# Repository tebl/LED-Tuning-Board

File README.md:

# LED Tuning Board

If you were to take a look at many of my repositories, you'll find that for someone who doesn't actually love having a bunch of LEDs on things, I seem to tell people to use a *whole* lot of them. There are projects where I've gone through several revisions, installing different colours on them so that I'd instantly be able to tell them apart. What you won't find is a lot of datasheets, because where I shop - you generally get a bag full of them, and nothing that you would call a datasheet. Perhaps I should shop in better places, but I just can't stop myself. And as for the end result, there are times where I'm straight up guessing at which value resistor to put in series with it. Sometimes it fails to light up, sometimes it'll blind people in the next room, and from time to time I get them *just right* because I had found the same bag of LEDs.

And after doing that for almost a decade, I knew it was time! It was time to change, it was time to get a variable bench power supply and a proper breadboard. Realizing that such PSUs cost far more than I would be willing to pay, and that I would never find a breadboard that I would consider *"good"*, I did what I always do: I designed something. I call it the *LED Tuning Board*.

Does it tune your LEDs? No. What it does is give you a way to quickly plug in various types of through-hole LEDs, and then allows you to quickly go through various combinations of resistors until you find something that *YOU* will find comfortable. Because *comfortable* is what you'll be willing to have sitting on your desk, no matter if that desk is in a brightly lit studio or the dank type of basements that I regularly seem to enjoy dwelling within.

At some point I wanted to do a whole video on the topic of the *LED Tuning Board*, but I miserably failed at coming up with sufficient amounts of puns in order to pull off 20 minutes worth of soldering an LED in different ways. Until I do, here's a short clip of me showing the thing in as short a time possible. RGB LEDs are a feature of it, but necessarily so - they're just three LEDs combined into the physical space of one. There are three *banks* of resistors, one for each - with a jumper next to it that hooks that end up to VCC or GND. Add more than one jumper to a single bank in order to put resistors in parallel, add a few DuPont wires between pins and you can easily put a banks resistor value in series with that of another bank.

Truly exciting stuff! And on that note, I also put a commonly available fuse on the board - for when things become slightly too exciting. 

# 1> Building the board
Soldering together the few components should be easy going as long as you have access to a reasonable set of tools, personally I'm using a cheap soldering station with adjustable temperature so there's no need really no need to offer up your hard-earned cash to the old Norse god, Hakko. Hakko is actually a well-known brand, not a Norse god as previously stated. I meant that as a joke, so please don't send me brand new Hakko gear as punishment (I would just end up using it). Go expensive if you want to, not because that one guy on the Internet told you to. Personally I prefer using 60/40 soldering tin, mostly as the lead-free stuff makes the job a lot harder when you're just getting into the hobby of soldering things together.

:warning: The subsequent images from the actual build process  were based on revision A of the project, this preview is of the updated design. The purpose of the change was to make the illustrations easier to read and understand, beyond that there are no changes. Enjoy building a copy of it that's better than the one I have!

Do, however, make sure to start by studying the PCB by itself. Both sides, perform dry fits where needed so that you have an idea of where everything should go. The latter is because removing a components is always a lot harder than getting it right in the first place. In particular, take care when it comes to the orientation of polarized components - these include electrolytic capacitors and diodes (match the orientation exactly, study the gallery images for reference). 

As for a first step though, I've just gone ahead and added the resistors to each of the resistor *banks*. While you could adapt things slightly by changing out some of the values, these are the most common values that anyone would probably have available in their parts-bin. Each of them should match up with a step on the pin header block next to it.

As for the remainder of the installation, I went in the direction of building a different version of the one covered by the schematic. Mainly because I did not have the LM317 variable regulator available when building it, so I instead made changes to the circuit by building one with a 3.3v regulator instead. Check out the proceeding subheadings for details on the construction of either of them.

Before doing all that, I did add a 1N5819 Schottky diode - that's there to keep things from exploding if you were to plug in a power supply with the incorrect polarity. For that you also need to ensure that you actually install it the right way, meaning that the little silver stripe should match up with the white stripe on the board.

## 1.1> 3.3v fixed regulator
My choice of the *LD1117AV33*, a 3.3v regulator, was based on the thorough research of finding one in my parts-bin then throwing it in there. As they're not entirely the same, we'll need to make a few small adjustments when attempting to use it.

The first change is that C2 should have a greater value than the one printed, going up to 10uF instead of the sticking with the 1uF as marked. The resistors marked from R1 through R4 have also been skipped, we also no longer have a need for J3. We also need to install a small piece of wire on the back, some of the leftover clippings from one of resistors will be perfect.

:grey_question: The LD1117A-series of volage regulators have a wide range of output voltages available, I've simply picked 3.3v as with a 5v power input I end up with the two I need. If you want something else, there's also the *LD1117AV50* in case you explicitly wanted one that has 5v on the output.

## 1.2>  Variable voltage regulator
The *LM317* voltage regulator is the one I had in mind when building this version of the PCB, its main selling point is that we can easily generate several other voltages based on the choice of resistors installed on the board. With a common resistor (R1) as its base, we will get different selectable output voltages (V1/V2/V3) depending on the value of resistors R2, R3 and R4 - one for each of the generated outputs. One has been filled in for you along with a set base, that's R1 at 240 Ohm and R2 at 390 Ohm for a V1 = 3.28v.

That sounds like a lot of math that we need to do, but if you're going by the one suggested - we've already chosen a base resistor value (R1 = 240 Ohm). Basically we just need to pick whatever we want for R3/R4 by going up or down on the table, just know that we won't be able to generate a higher voltage than what we sufficiently provide it with. If you want to understand how exactly it works, either consult the datasheet included or you can go to the source of the table at [reuk.co.uk](http://www.reuk.co.uk/wordpress/electric-circuit/lm317-voltage-calculator/) for all of the relevant mathematical questions.

## 1.3> Moving on
With all of the neat details on the choice of voltage regulators taken care of, hopefully explained sufficiently that you know what was going on the whole time. As for the pictures we've been covering the installation of a fixed regulator, so when moving forwards we need to keep in mind that J3 will not be needed. You will, however, need it if you went with the variable option. 

Moving on with the installation, we've then done is to add all of the pin headers that are required. I've tried splashing a bit of colour here and there, mostly so that I remember that the red ones are the ones that requires that we know what we're doing (linking the block to either VCC on top, or GND on the bottom). The yellow are for enabling a block, if you want to measure current usage then you would put your meter on each of these two pins - otherwise, replacing it with a jumper cap. The black are always linked horizontally, choosing a specific resistor value, input voltage or chosen variable voltage.

If you've installed some like it before, you've no doubt already altered your fingerprint by trying to hold to one while doing so. Heat travels, and to put your finger on the other side while soldering it means that your finger will reach the set soldering iron shortly thereafter. They will go crooked, so my method is just to tack them mostly into place then reheat with a better grip afterwards - then solder the others. Perfect result, one \*ouch\* at a time!

Next step accounts for the rest, so we're just adding a *2.1mm x 5.1mm barrel* socket for input power as well as cheap 5x20mm glass fuse holder. As for the latter some of them will come without the plastic shroud and need to be installed with a fuse in it, at least that's what I find to be easiest.

For the pièce de résistance, I'm using the cheapest 16-pin ZIF-socket known to man. I don't know if it remains the cheapest, but it was when I ordered it - and that makes it perfect for abuse on projects such as this one. Just remember to install it with the socket handle pointing towards the right. As for what the socket pins are used for, it's various types of LEDs and the way they're wired can be seen on the illustration below it (in a way that's slightly easier on later revisions).

With that we've just added our selection of jumper caps so that'd we have something to play around with. J2 here is set to *ADJ* so that we're taking our LED power input from the regulator, in the other position we're wired straight to whatever comes through the fuse and the slight drop from the power diode. As for what comes next, just plug some random LEDs into it and start moving the green jumpers, as shown in the picture, up and down until you find your favorite setting.

Congratulations! You've just managed to make it through to the end, a whole thing just to pick a single resistor value to use for your project (or one of mine).

## 1.4> For extra credit
For extra credit, you can also solder one of the cheaply available voltage display modules to the relevant test-points. That way you won't even need to dust off your multimeter when making sure that the voltage has been set correctly, especially when you're using the adjustable voltage regulator. Fix to the board using double-sided tape, wherever you think it'll fit. Here's where I put mine:

# Schematic
The supplied KiCad files should be sufficient as both a schematic and as a  starting point for ordering PCBs (basically you could just zip the contents of the export folder and upload that on a fabrication site), the schematic is also available in [PDF-format](https://github.com/tebl/LED-Tuning-Board/tree/main/documentation/schematic) and this is what you'll need to print and work your way through this things don't work as expected after assembly.

# BOM
Most parts should be easy to get a hold of from your favorite local electronic component shop, but given that I don't have access to such shops where I live so everything was based on whatever I could get cheapest from eBay/AliExpress (free shipping, plan on usually waiting 3-4 weeks though). The list below should be everything you'll need in addition to a workable soldering iron and some 60/40 soldering tin.

Note that some pin references will have a note attached to it, these are found below the table. In particular these are relevant for duplicated references, one for each of the two regulator options described in the documentation (you will only need one set).

| Reference     | Item                                                | Count | Order     |
| ------------- | --------------------------------------------------- | ----- | --------- |
| PCB           | Fabricate using Gerber files                        |     1 | [PCBWay](https://www.pcbway.com/project/shareproject/LED_Tuning_Board_fdd33131.html)
| C1            | 100nF capacitor (5mm pin spacing)                   |     1 |
| C2 *1         | 1uF electrolytic capacitor (2mm pin spacing)        |     1 |
| C2 *2         | 10uF electrolytic capacitor (2mm pin spacing)       |     1 |
| D1            | 1N5819 Schottky diode (DO-41)                       |     1 |
| F1            | 5x20mm fuse holder (add 1A fast blow fuse)          |     1 |
| J1            | 2.1mm x 5.5mm barrel socket                         |     1 |
| J2            | 2x2 pin 2.54mm dual row straight header segment     |     1 |
| J3 *1         | 2x3 pin 2.54mm dual row straight header segment     |     1 |
| J4-J6         | 2x8 pin 2.54mm dual row straight header segment     |     3 |
| JP1,JP3,JP4   | 1x3 pin 2.54mm straight header segment              |     3 |
| JP2,JP5,JP6   | 1x2 pin 2.54mm straight header segment              |     3 |
| R1 *1         | 240 Ohm resistor                                    |     1 |
| R2 *1         | 390 Ohm resistor                                    |     1 |
| R3,R4 *1      | Choose suitable resistor value                      |     2 |
| R5,R13,R21    | 100 Ohm resistor                                    |     3 |
| R6,R14,R22    | 220 Ohm resistor                                    |     3 |
| R7,R15,R23    | 330 Ohm resistor                                    |     3 |
| R8,R16,R24    | 470 Ohm resistor                                    |     3 |
| R9,R17,R25    | 680 Ohm resistor                                    |     3 |
| R10,R18,R26   | 1k Ohm resistor                                     |     3 |
| R11,R19,R27   | 2k2 (2200) Ohm resistor                             |     3 |
| R12,R20,R28   | 3k3 (3300) Ohm resistor                             |     3 |
| U1 *1         | LM317 adjustable voltage regulator (TO-220)         |     1 |
| U1 *2         | LD1117AV33 fixed 3.3v voltage regulator (TO-220)    |     1 |
| U2            | 16-pin ZIF-socket                                   |     1 |
|               | Pin header jumper caps, different colours as wanted |    10 |

1) These account for the components used when installing a variable voltage regulator, follow the documentation for sizing the resistor without a specified voltage. Also, see *2 for a fixed regulator option.
2) These are used for a 3.3v fixed voltage regulator, you would then no longer need those marked *1. For more information see documentation on building the device.

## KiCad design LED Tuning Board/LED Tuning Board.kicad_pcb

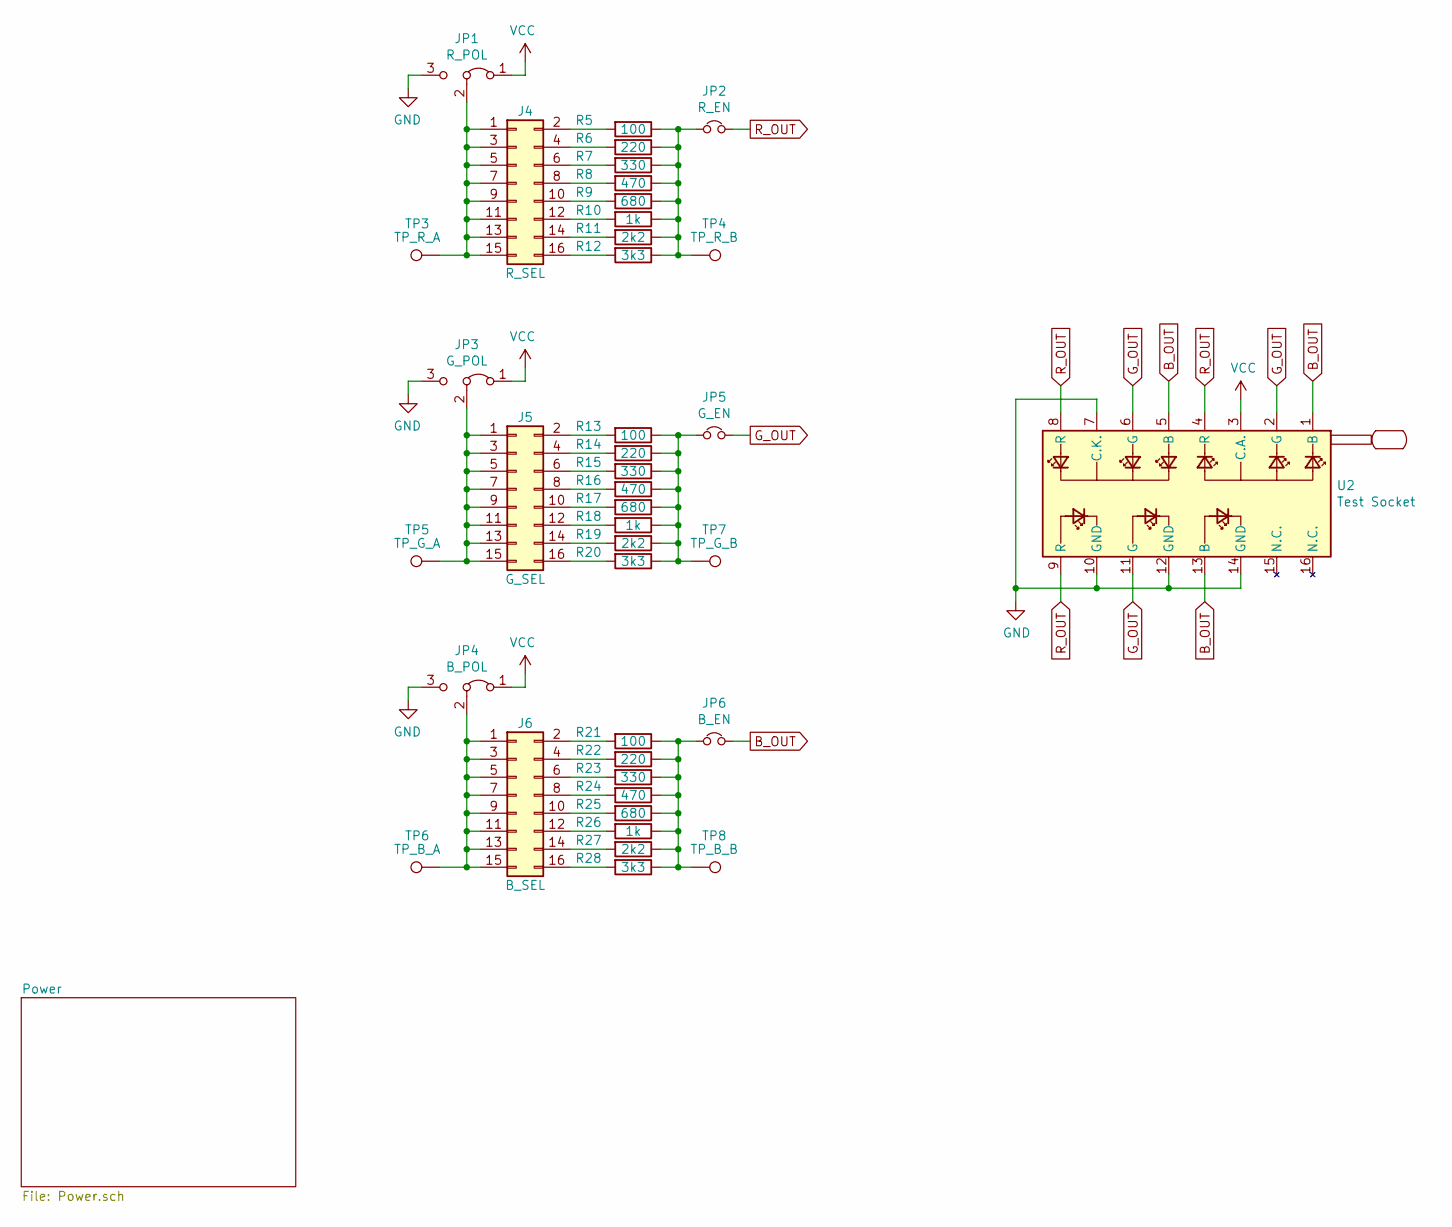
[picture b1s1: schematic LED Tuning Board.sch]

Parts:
J4: R_SEL; PinHeader_2x08_P2.54mm_Vertical
J5: G_SEL; PinHeader_2x08_P2.54mm_Vertical
J6: B_SEL; PinHeader_2x08_P2.54mm_Vertical
JP1: R_POL; PinHeader_1x03_P2.54mm_Vertical
JP2: R_EN; PinHeader_1x02_P2.54mm_Vertical
JP3: G_POL; PinHeader_1x03_P2.54mm_Vertical
JP4: B_POL; PinHeader_1x03_P2.54mm_Vertical
JP5: G_EN; PinHeader_1x02_P2.54mm_Vertical
JP6: B_EN; PinHeader_1x02_P2.54mm_Vertical
R5, R13, R21: 100; R_Axial_DIN0207_L6.3mm_D2.5mm_P10.16mm_Horizontal
R6, R14, R22: 220; R_Axial_DIN0207_L6.3mm_D2.5mm_P10.16mm_Horizontal
R7, R15, R23: 330; R_Axial_DIN0207_L6.3mm_D2.5mm_P10.16mm_Horizontal
R8, R16, R24: 470; R_Axial_DIN0207_L6.3mm_D2.5mm_P10.16mm_Horizontal
R9, R17, R25: 680; R_Axial_DIN0207_L6.3mm_D2.5mm_P10.16mm_Horizontal
R10, R18, R26: 1k; R_Axial_DIN0207_L6.3mm_D2.5mm_P10.16mm_Horizontal
R11, R19, R27: 2k2; R_Axial_DIN0207_L6.3mm_D2.5mm_P10.16mm_Horizontal
R12, R20, R28: 3k3; R_Axial_DIN0207_L6.3mm_D2.5mm_P10.16mm_Horizontal
TP3: TP_R_A; TestPoint
TP4: TP_R_B; TestPoint
TP5: TP_G_A; TestPoint
TP6: TP_B_A; TestPoint
TP7: TP_G_B; TestPoint
TP8: TP_B_B; TestPoint
U2: Test Socket; DIP_Socket-16_W4.3_W5.08_W7.62_W10.16_W10.9_3M_216-3340-00-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

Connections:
B_OUT: JP6.2, U2.1 (B), U2.5 (B), U2.13 (B)
GND: JP1.3 (B), JP3.3 (B), JP4.3 (B), U2.7 (C.K.), U2.10 (GND), U2.12 (GND), U2.14 (GND); also elsewhere on the board
G_OUT: JP5.2, U2.2 (G), U2.6 (G), U2.11 (G)
unnamed: J4.1, J4.3, J4.5, J4.7, J4.9, J4.11, J4.13, J4.15, JP1.2 (C), TP3.1
unnamed: J4.2, R5.2
unnamed: J4.4, R6.2
unnamed: J4.6, R7.2
unnamed: J4.8, R8.2
unnamed: J4.10, R9.2
unnamed: J4.12, R10.2
unnamed: J4.14, R11.2
unnamed: J4.16, R12.2
unnamed: J5.1, J5.3, J5.5, J5.7, J5.9, J5.11, J5.13, J5.15, JP3.2 (C), TP5.1
unnamed: J5.2, R13.2
unnamed: J5.4, R14.2
unnamed: J5.6, R15.2
unnamed: J5.8, R16.2
unnamed: J5.10, R17.2
unnamed: J5.12, R18.2
unnamed: J5.14, R19.2
unnamed: J5.16, R20.2
unnamed: J6.1, J6.3, J6.5, J6.7, J6.9, J6.11, J6.13, J6.15, JP4.2 (C), TP6.1
unnamed: J6.2, R21.2
unnamed: J6.4, R22.2
unnamed: J6.6, R23.2
unnamed: J6.8, R24.2
unnamed: J6.10, R25.2
unnamed: J6.12, R26.2
unnamed: J6.14, R27.2
unnamed: J6.16, R28.2
unnamed: JP2.1, R5.1, R6.1, R7.1, R8.1, R9.1, R10.1, R11.1, R12.1, TP4.1
unnamed: JP5.1, R13.1, R14.1, R15.1, R16.1, R17.1, R18.1, R19.1, R20.1, TP7.1
unnamed: JP6.1, R21.1, R22.1, R23.1, R24.1, R25.1, R26.1, R27.1, R28.1, TP8.1
R_OUT: JP2.2, U2.4 (R), U2.8 (R), U2.9 (R)
VCC: JP1.1 (A), JP3.1 (A), JP4.1 (A), U2.3 (C.A.); also elsewhere on the board

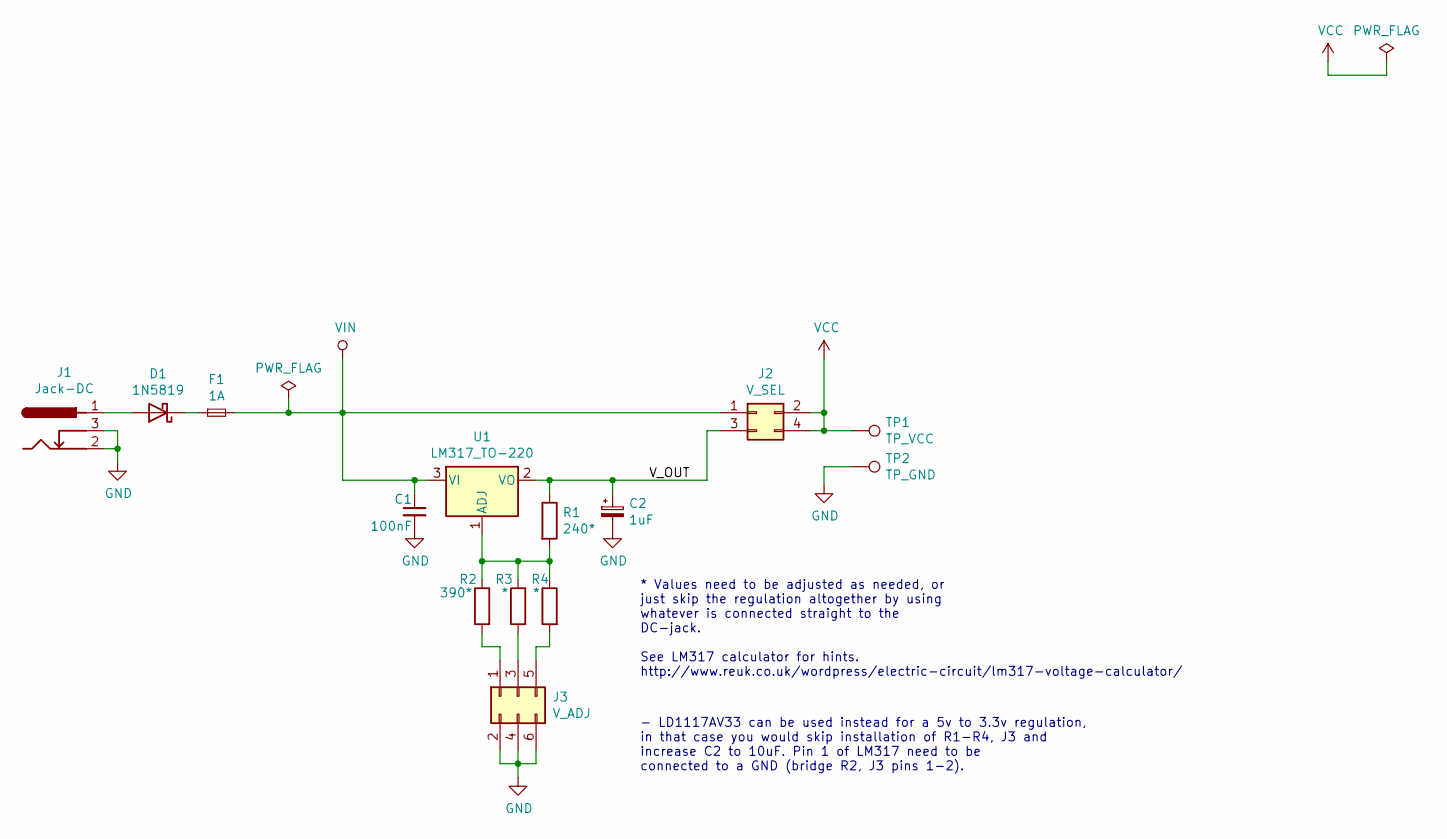
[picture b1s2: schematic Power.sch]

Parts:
C1: 100nF; C_Disc_D4.7mm_W2.5mm_P5.00mm
C2: 1uF; CP_Radial_D4.0mm_P2.00mm
D1: 1N5819; D_DO-41_SOD81_P10.16mm_Horizontal
F1: 1A; Fuseholder5x20_horiz_SemiClosed_Casing10x25mm
J1: Jack-DC; BARREL_JACK
J2: V_SEL; PinHeader_2x02_P2.54mm_Vertical
J3: V_ADJ; PinHeader_2x03_P2.54mm_Vertical
R1: 240*; R_Axial_DIN0207_L6.3mm_D2.5mm_P10.16mm_Horizontal
R2: 390*; R_Axial_DIN0207_L6.3mm_D2.5mm_P10.16mm_Horizontal
R3, R4: *; R_Axial_DIN0207_L6.3mm_D2.5mm_P10.16mm_Horizontal
TP1: TP_VCC; TestPoint_Large
TP2: TP_GND; TestPoint_Large
U1: LM317_TO-220; TO-220-3_Horizontal_TabDown

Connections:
/Power/V_OUT: C2.1, J2.3, R1.1, U1.2 (VO)
GND: C1.2, C2.2, J1.2, J1.3, J3.2, J3.4, J3.6, TP2.1; also elsewhere on the board
unnamed: D1.1 (K), F1.1
unnamed: D1.2 (A), J1.1
unnamed: J3.1, R2.2
unnamed: J3.3, R3.2
unnamed: J3.5, R4.2
unnamed: R1.2, R2.1, R3.1, R4.1, U1.1 (ADJ)
VCC: J2.2, J2.4, TP1.1; also elsewhere on the board
VIN: C1.1, F1.2, J2.1, U1.3 (VI)

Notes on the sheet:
* Values need to be adjusted as needed, or just skip the regulation altogether by using whatever is connected straight to the DC-jack. See LM317 calculator for hints. http://www.reuk.co.uk/wordpress/electric-circuit/lm317-voltage-calculator/
- LD1117AV33 can be used instead for a 5v to 3.3v regulation, in that case you would skip installation of R1-R4, J3 and increase C2 to 10uF. Pin 1 of LM317 need to be connected to a GND (bridge R2, J3 pins 1-2).

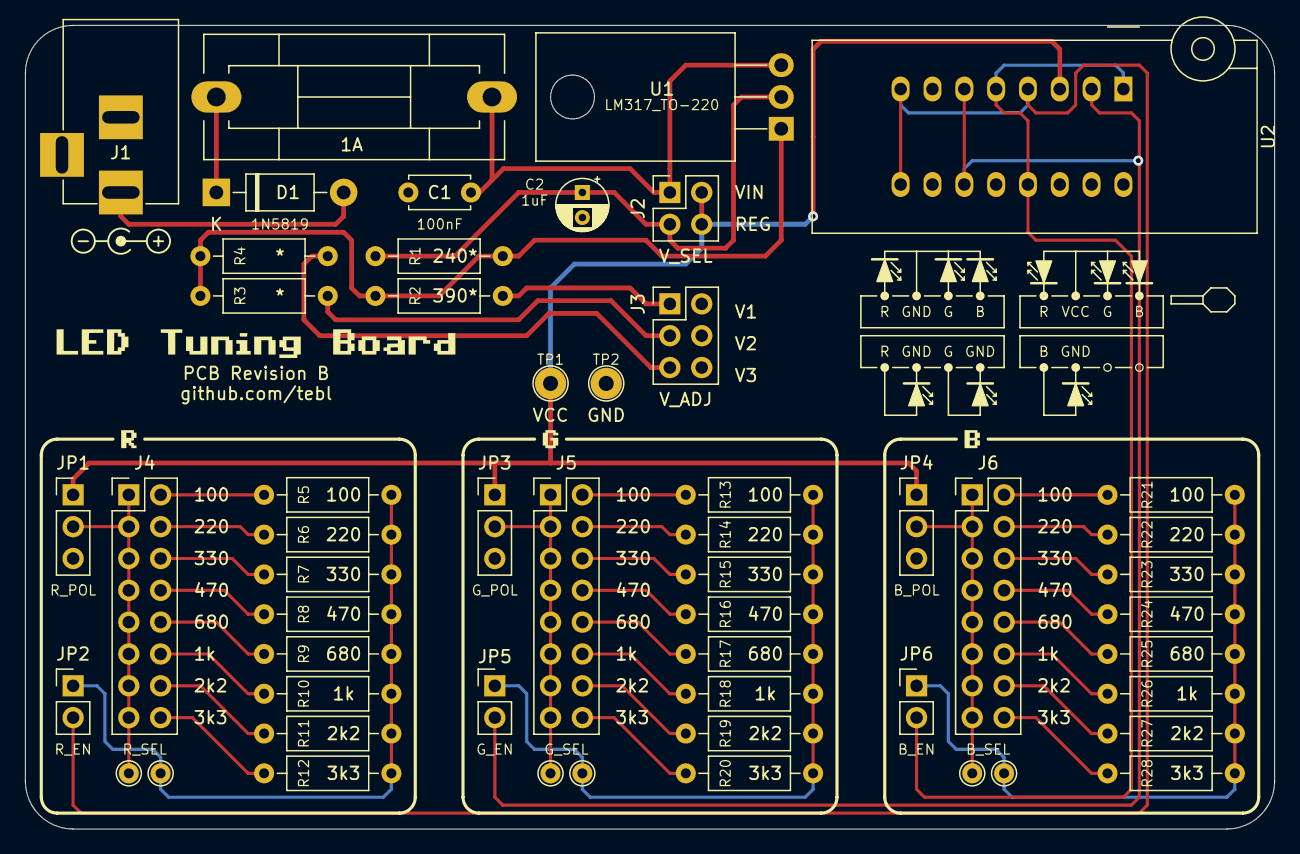
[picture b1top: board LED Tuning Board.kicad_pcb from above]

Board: 2 copper layers, 99.7 x 64.1 mm, 54 parts (0 on the bottom side), 43 nets.

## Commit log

2023-04-11 First schematic draft
2023-04-12 Added layout
2023-04-13 Datasheet
2023-09-07 Update pictures
2023-09-07 Slight tweaks
2024-10-13 Add image
2024-10-13 Resize images
2024-10-14 Add README
2024-10-14 Updated picture
2024-10-14 Jumper caps forgotten, now found.
2024-10-14 Export files
